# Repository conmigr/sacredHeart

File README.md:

# sacredHeart
Open deveopment platform heart shape PCB

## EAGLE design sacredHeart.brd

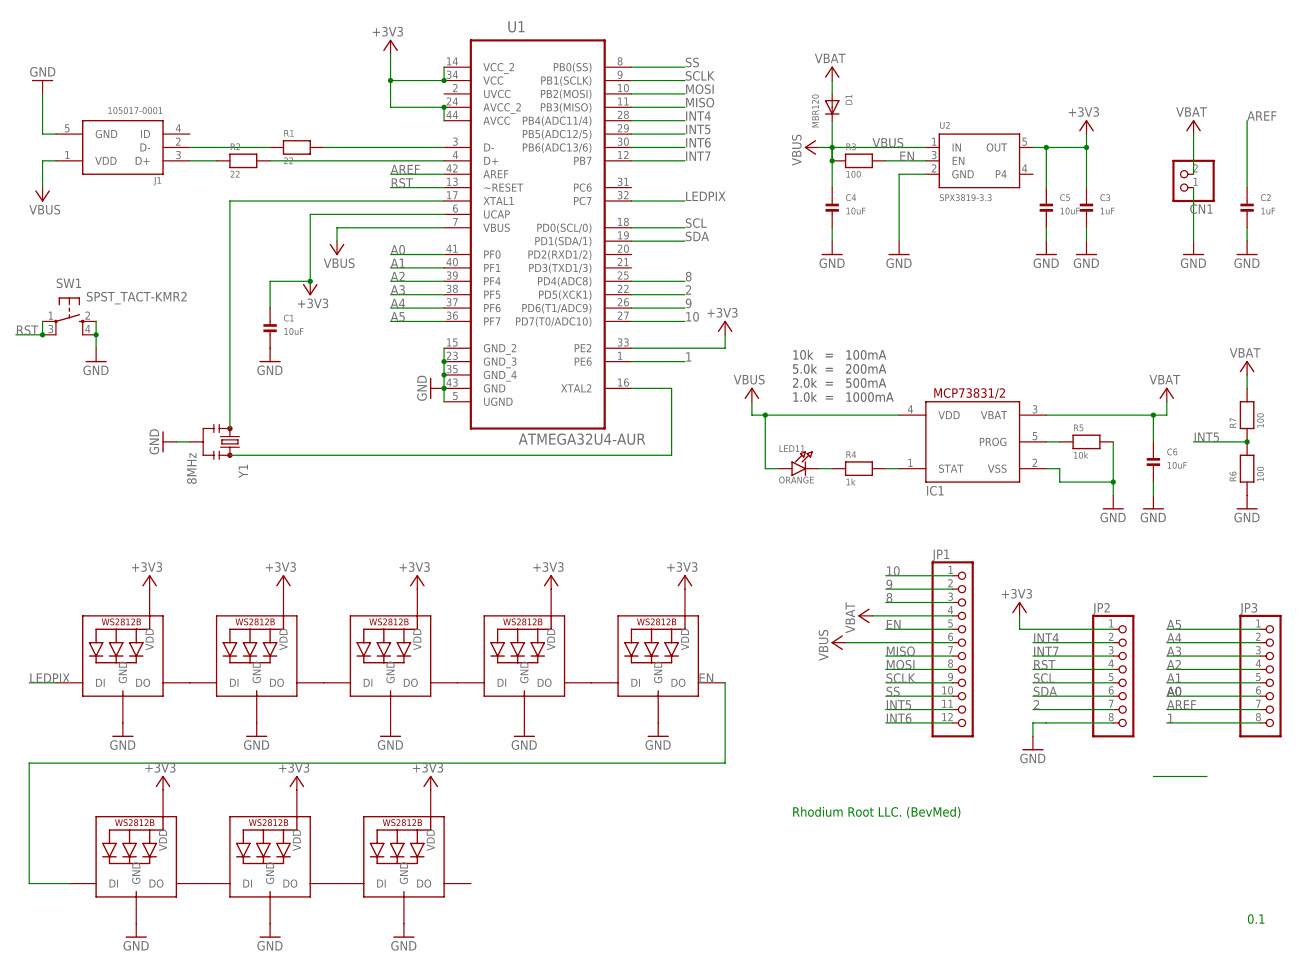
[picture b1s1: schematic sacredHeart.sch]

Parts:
C1, C4, C5, C6: 10uF; 0805
C2, C3: 1uF; 0805
CN1: JST_2PIN; JSTPH2
D1: MBR120; SOD-123
IC1: MCP73831/OT; SOT23-5L
J1: 105017-0001; MOLEX_105017-0001
JP1: HEADER-1X12; 1X12_ROUND
JP2, JP3: HEADER-1X8ROUND; 1X08_ROUND
LED1, LED2, LED3, LED4, LED5, LED6, LED7, LED8: WS2812B3535; LED3535
LED11: ORANGE; CHIPLED_0805_NOOUTLINE
R1, R2: 22; 0603
R3, R6, R7: 100; 0603
R4: 1k; 0603
R5: 10k; 0603
SW1: SPST_TACT-KMR2; KMR2
U1: ATMEGA32U4-AUR; QFP80P1200X1200X120-44N
U2: SPX3819-3.3; SOT23-5
Y1: 8MHz; RESONATOR-SMD-3.2X1.3

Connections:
1: JP3.8, U1.1 (PE6)
2: JP2.7, U1.22 (PD5(XCK1))
8: JP1.3, U1.25 (PD4(ADC8))
9: JP1.2, U1.26 (PD6(T1/ADC9))
10: JP1.1, U1.27 (PD7(T0/ADC10))
+3V3: C1.1, C3.1, C5.1, JP2.1, LED1.2 (VDD), LED2.2 (VDD), LED3.2 (VDD), LED4.2 (VDD), LED5.2 (VDD), LED6.2 (VDD), LED7.2 (VDD), LED8.2 (VDD), U1.6 (UCAP), U1.14 (VCC_2), U1.24 (AVCC_2), U1.33 (PE2), U1.34 (VCC), U1.44 (AVCC), U2.5 (OUT)
A0: JP3.6, U1.41 (PF0)
A1: JP3.5, U1.40 (PF1)
A2: JP3.4, U1.39 (PF4)
A3: JP3.3, U1.38 (PF5)
A4: JP3.2, U1.37 (PF6)
A5: JP3.1, U1.36 (PF7)
AREF: C2.1, JP3.7, U1.42 (AREF)
EN: JP1.5, R3.2, U2.3 (EN)
GND: C1.2, C2.2, C3.2, C4.2, C5.2, C6.2, CN1.1, IC1.2 (VSS), J1.5 (GND), JP2.8, LED1.4 (GND), LED2.4 (GND), LED3.4 (GND), LED4.4 (GND), LED5.4 (GND), LED6.4 (GND), LED7.4 (GND), LED8.4 (GND), R5.2, R6.1, SW1.2 (S), SW1.4 (S1), U1.5 (UGND), U1.15 (GND_2), U1.23 (GND_3), U1.35 (GND_4), U1.43 (GND), U2.2 (GND), Y1.2
INT4: JP2.2, U1.28 (PB4(ADC11/4))
INT5: JP1.11, R6.2, R7.1, U1.29 (PB5(ADC12/5))
INT6: JP1.12, U1.30 (PB6(ADC13/6))
INT7: JP2.3, U1.12 (PB7)
LEDPIX: LED1.1 (DI), U1.32 (PC7)
MISO: JP1.7, U1.11 (PB3(MISO))
MOSI: JP1.8, U1.10 (PB2(MOSI))
unnamed: IC1.5 (PROG), R5.1
unnamed: R1.2, U1.3 (D-)
unnamed: LED2.3 (DO), LED3.1 (DI)
unnamed: LED3.3 (DO), LED4.1 (DI)
unnamed: IC1.1 (STAT), R4.2
unnamed: LED11.C, R4.1
unnamed: R2.2, U1.4 (D+)
unnamed: J1.2 (D-), R1.1
unnamed: J1.3 (D+), R2.1
unnamed: U1.16 (XTAL2), Y1.3
unnamed: U1.17 (XTAL1), Y1.1
unnamed: LED1.3 (DO), LED2.1 (DI)
unnamed: LED7.3 (DO), LED8.1 (DI)
unnamed: LED6.3 (DO), LED7.1 (DI)
unnamed: LED4.3 (DO), LED5.1 (DI)
unnamed: LED5.3 (DO), LED6.1 (DI)
RST: JP2.4, SW1.1, SW1.3 (P1), U1.13 (~RESET)
SCL: JP2.5, U1.18 (PD0(SCL/0))
SCLK: JP1.9, U1.9 (PB1(SCLK))
SDA: JP2.6, U1.19 (PD1(SDA/1))
SS: JP1.10, U1.8 (PB0(SS))
UVCC: U1.2 (UVCC)
VBAT: C6.1, CN1.2, D1.A, IC1.3 (VBAT), JP1.4, R7.2
VBUS: C4.1, D1.C, IC1.4 (VDD), J1.1 (VDD), JP1.6, LED11.A, R3.1, U1.7 (VBUS), U2.1 (IN)

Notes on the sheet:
0.1
Rhodium Root LLC. (BevMed)
10k = 100mA 5.0k = 200mA 2.0k = 500mA 1.0k = 1000mA

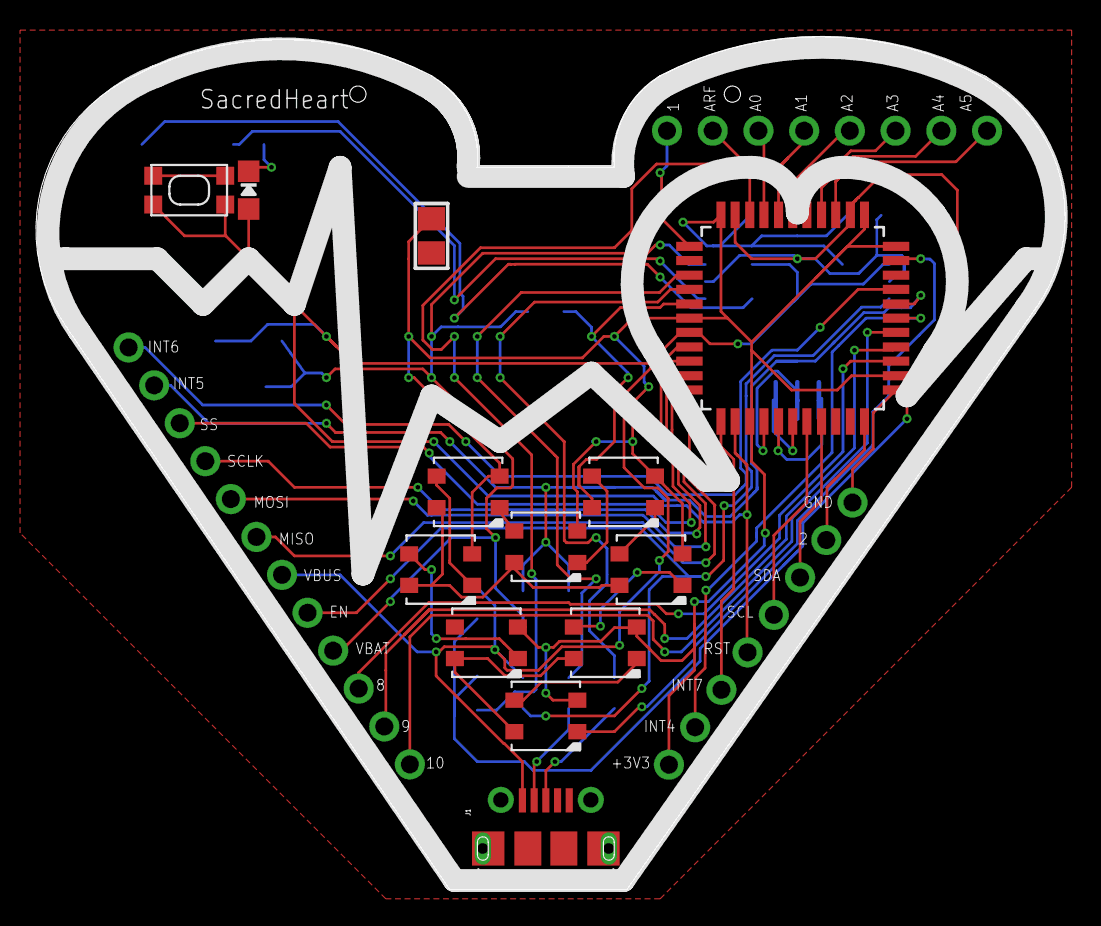
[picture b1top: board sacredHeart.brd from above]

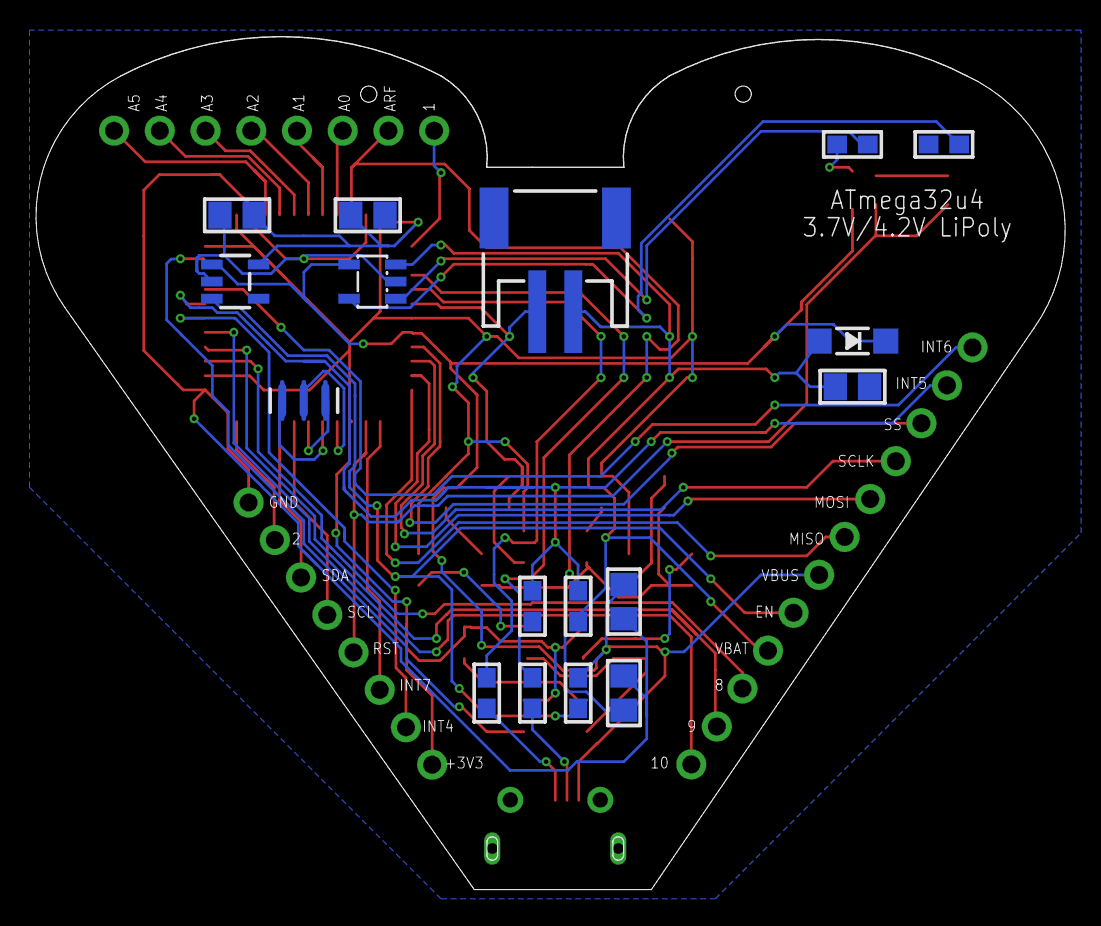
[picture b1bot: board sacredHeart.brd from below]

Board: 2 copper layers, 57.1 x 47.3 mm, 33 parts (17 on the bottom side), 45 nets.

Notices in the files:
parts and their libraries:
microbuilder: This work is placed in the public domain, and may be freely used for commercial and non-commercial work with the following conditions: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
SparkFun-Clocks: Licensing: Creative Commons ShareAlike 4.0 International - https://creativecommons.org/licenses/by-sa/4.0
